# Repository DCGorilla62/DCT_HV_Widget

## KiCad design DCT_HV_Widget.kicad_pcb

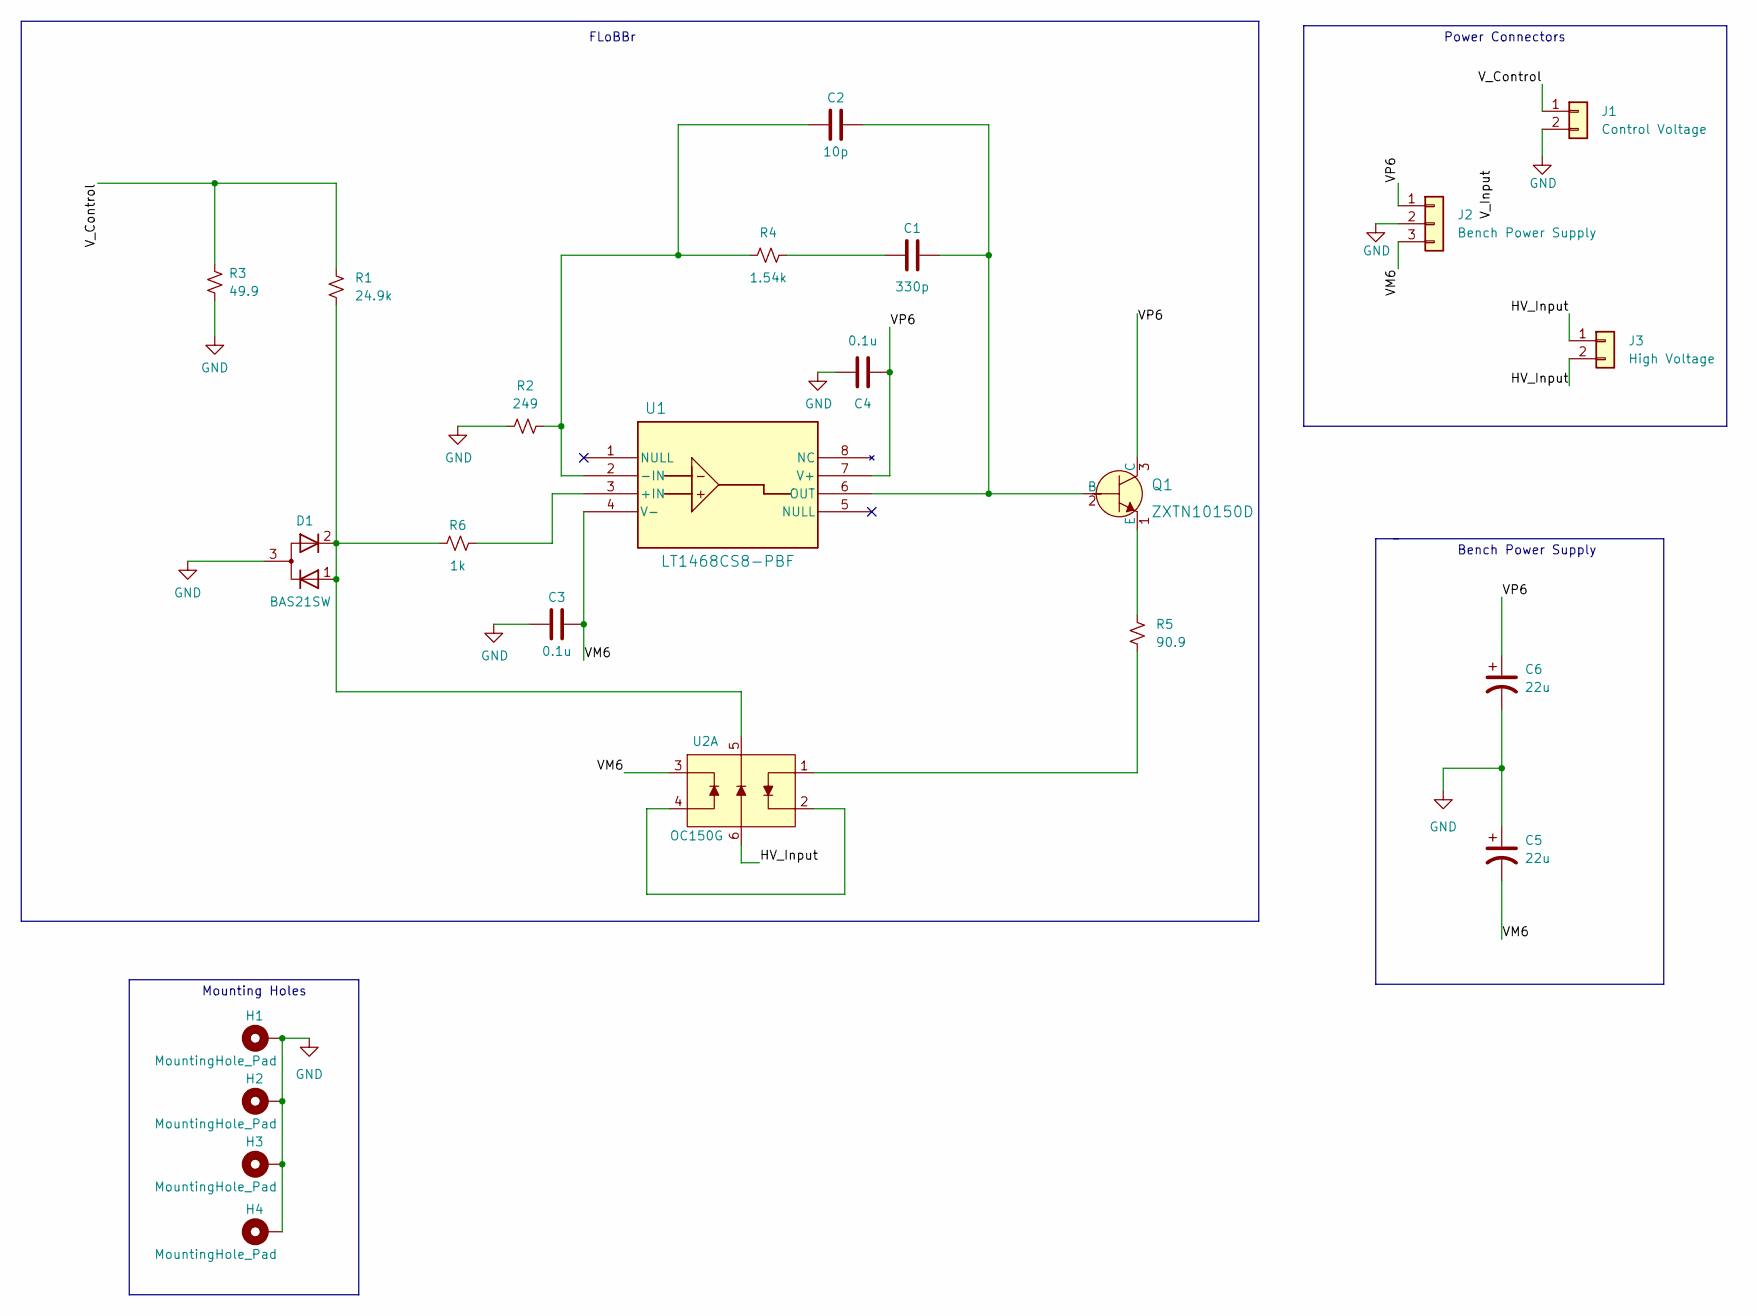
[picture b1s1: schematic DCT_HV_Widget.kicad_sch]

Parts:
C1: 330p; C_0603_1608Metric
C2: 10p; C_0603_1608Metric
C3, C4: 0.1u; C_0603_1608Metric
C5, C6: 22u; CP_EIA-3528-21_Kemet-B
D1: BAS21SW
H1, H2, H3, H4: MountingHole_Pad; MountingHole_3.2mm_M3_Pad
J1: Control Voltage; Molex_Micro-Fit_3.0_43650-0200_1x02_P3.00mm_Horizontal
J2: Bench Power Supply; Molex_Micro-Fit_3.0_43650-0300_1x03_P3.00mm_Horizontal
J3: High Voltage; Molex_Micro-Fit_3.0_43650-0200_1x02_P3.00mm_Horizontal
Q1: ZXTN10150D; ZXTN10150DZ; MPN 2N2219A; Digi-Key_PN 2N2219ACS-ND
R1: 24.9k; R_0603_1608Metric
R2: 249; R_0603_1608Metric
R3: 49.9; R_0603_1608Metric
R4: 1.54k; R_0603_1608Metric
R5: 90.9; R_Axial_DIN0207_L6.3mm_D2.5mm_P10.16mm_Horizontal
R6: 1k; R_0603_1608Metric
U1: LT1468CS8-PBF; LT1468CS8#PBF_SO-8_S_LIT
U2: OC150G; OC150G_v2

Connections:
/HV_Input: J3.1, J3.2, U2.6
/VM6: C3.2, C5.2, J2.3, U1.4 (V-), U2.3
/VP6: C4.1, C6.1, J2.1, Q1.3 (C), U1.7 (V+)
/V_Control: J1.1, R1.1, R3.1
GND: C3.1, C4.2, C5.1, C6.2, D1.3 (A), H1.1, H2.1, H3.1, H4.1, J1.2, J2.2, R2.1, R3.2
unnamed: C1.1, R4.2
unnamed: C1.2, C2.2, Q1.2 (B), U1.6 (OUT)
unnamed: C2.1, R2.2, R4.1, U1.2 (-IN)
unnamed: D1.1 (K), D1.2 (K), R1.2, R6.2, U2.5
unnamed: Q1.1 (E), R5.1
unnamed: R5.2, U2.1
unnamed: R6.1, U1.3 (+IN)
unnamed: U2.2, U2.4

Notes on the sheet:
Mounting Holes
Power Connectors
Bench Power Supply
FLoBBr

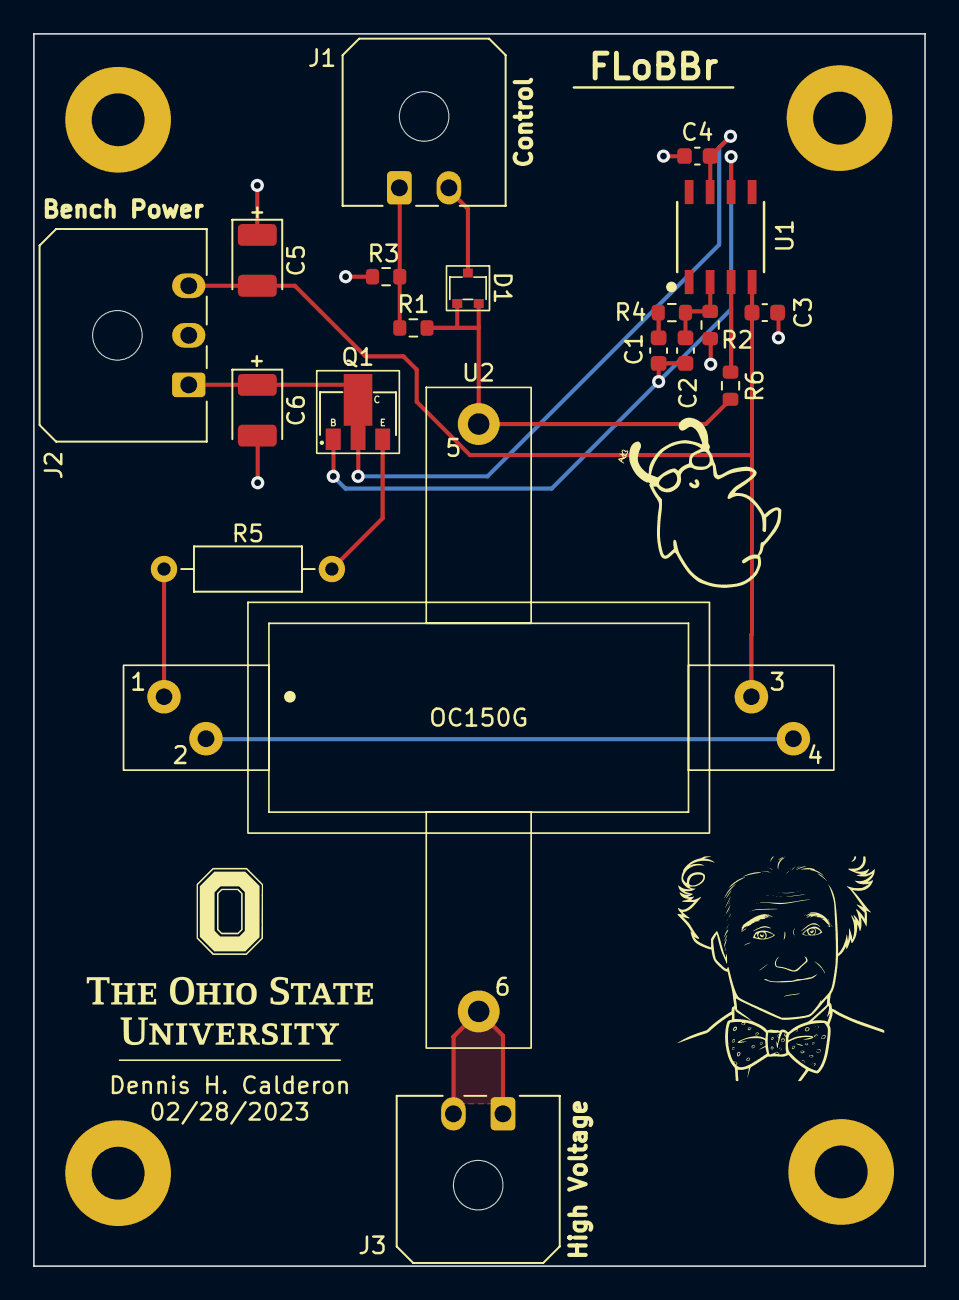
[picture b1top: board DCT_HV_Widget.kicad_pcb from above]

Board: 2 copper layers, 53.9 x 74.6 mm, 23 parts (0 on the bottom side), 13 nets.

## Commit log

2023-02-06 Footprint for OC150G created
2023-02-07 Began schematic. Added libraries for components
2023-02-07 Updated schematic.
2023-02-10 Updated schematic connecting pin 3 and pin 1 on BAS21SW diode
2023-02-10 Minor change to schematic
2023-02-13 Corrected OpAmp pins and updated LT1468
2023-02-13 Updated OC150G footprint
2023-02-16 Updated PCB layout
2023-02-16 Added .gitignore file
2023-02-16 Added gerber files
2023-02-16 Cleaned up repo a bit
2023-03-01 Updated PCB with Gerard feedback
2023-03-01 Updated PCB with silkscreens
2023-03-06 Updated PCB. Increased HV clearance. Added 0.6mm solder expansion. C2 closer to R4. Increased size of pin 1 marking for U1.
2023-03-07 Udpated PCB
2023-03-07 Updated PCB. Rearranged bottom silkscreen layer.
2023-03-07 Updated PCB. Rotated R4. Minimize distance between R4 and C2.
2023-03-07 Ready for fab. FLoBBr rev1
